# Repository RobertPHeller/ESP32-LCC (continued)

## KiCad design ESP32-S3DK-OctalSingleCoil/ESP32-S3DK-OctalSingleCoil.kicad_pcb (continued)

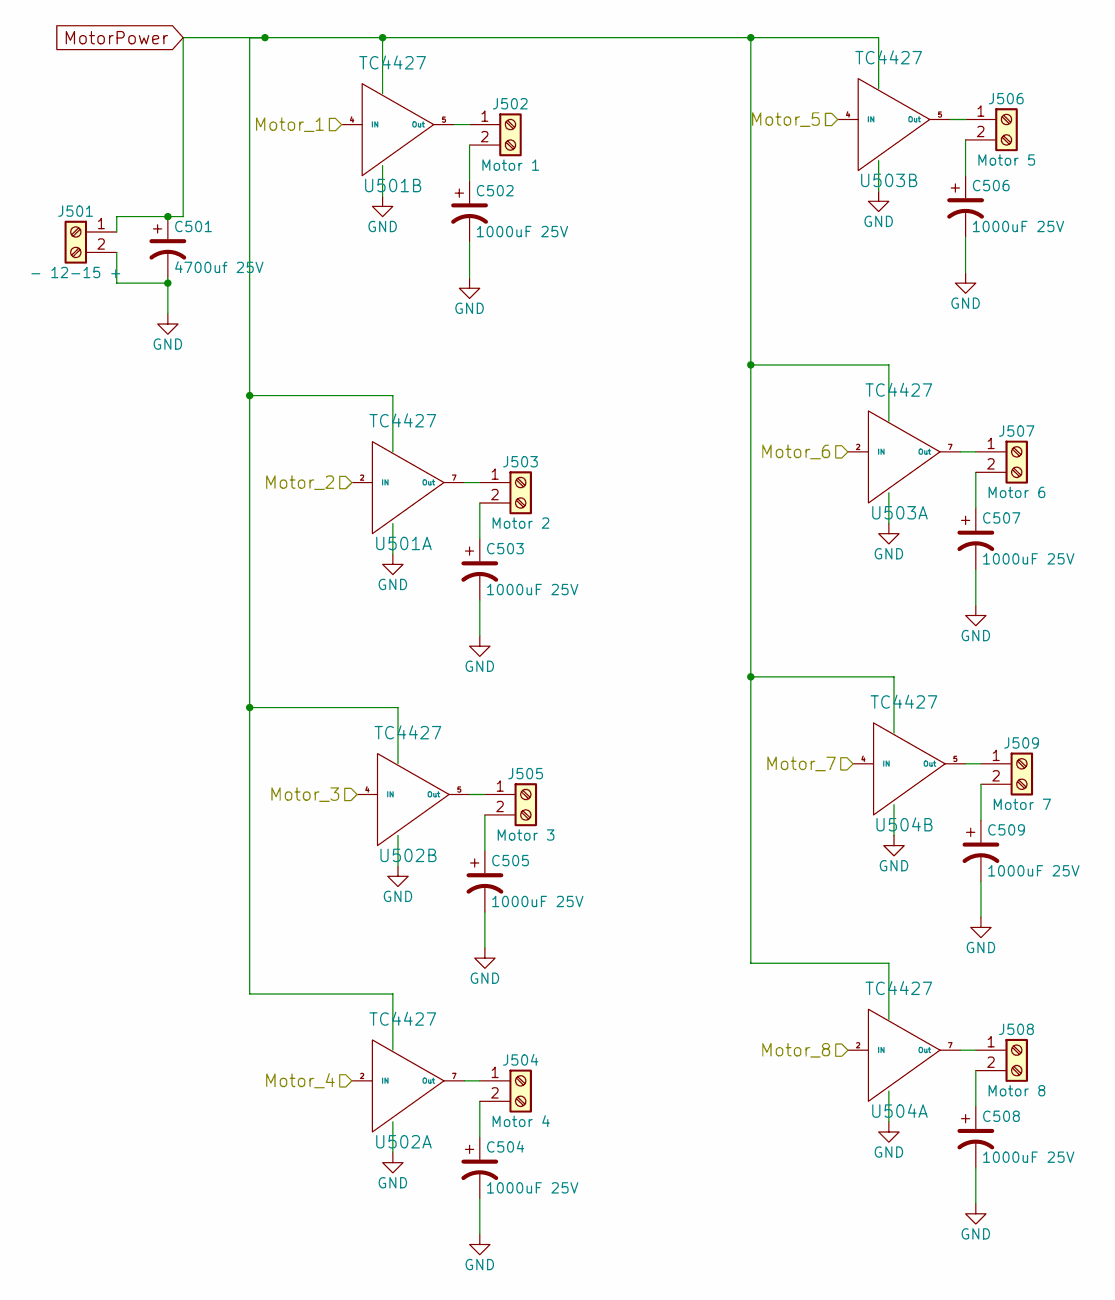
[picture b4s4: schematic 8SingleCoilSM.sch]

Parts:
C501: 4700uf 25V; EEEFK0J133SM; Mouser Part Number 667-EEE-FK1E472SM
C502, C503, C504, C505, C506, C507, C508, C509: 1000uF 25V; CP_Elec_10x10.5; Mouser Part Number 661-EMZS250ARA102MJA
J501: - 12-15 +; TerminalBlock_Pheonix_PT-3.5mm_2pol
J502: Motor 1; TerminalBlock_Pheonix_PT-3.5mm_2pol
J503: Motor 2; TerminalBlock_Pheonix_PT-3.5mm_2pol
J504: Motor 4; TerminalBlock_Pheonix_PT-3.5mm_2pol
J505: Motor 3; TerminalBlock_Pheonix_PT-3.5mm_2pol
J506: Motor 5; TerminalBlock_Pheonix_PT-3.5mm_2pol
J507: Motor 6; TerminalBlock_Pheonix_PT-3.5mm_2pol
J508: Motor 8; TerminalBlock_Pheonix_PT-3.5mm_2pol
J509: Motor 7; TerminalBlock_Pheonix_PT-3.5mm_2pol
U501, U502, U503, U504: TC4427; SOIC-8_3.9x4.9mm_Pitch1.27mm; Mouser Part Number 579-TC1427COA

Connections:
/MCU/GPIO3/Motor6: U503.2 (IN); also elsewhere on the board
/MCU/GPIO6/Motor1: U501.4 (IN); also elsewhere on the board
/MCU/GPIO7/Motor2: U501.2 (IN); also elsewhere on the board
/MCU/GPIO8/Motor5: U503.4 (IN); also elsewhere on the board
/MCU/GPIO9/Motor8: U504.2 (IN); also elsewhere on the board
/MCU/GPIO15/Motor3: U502.4 (IN); also elsewhere on the board
/MCU/GPIO16/Motor4: U502.2 (IN); also elsewhere on the board
/MCU/GPIO46/Motor7: U504.4 (IN); also elsewhere on the board
GND: C501.2, C502.2, C503.2, C504.2, C505.2, C506.2, C507.2, C508.2, C509.2, J501.2, U501.3 (GND), U502.3 (GND), U503.3 (GND), U504.3 (GND); also elsewhere on the board
MotorPower: C501.1, J501.1, U501.6 (Vdd), U502.6 (Vdd), U503.6 (Vdd), U504.6 (Vdd)
unnamed: C502.1, J502.2
unnamed: C503.1, J503.2
unnamed: C504.1, J504.2
unnamed: C505.1, J505.2
unnamed: C506.1, J506.2
unnamed: C507.1, J507.2
unnamed: C508.1, J508.2
unnamed: C509.1, J509.2
unnamed: J502.1, U501.5 (Out)
unnamed: J503.1, U501.7 (Out)
unnamed: J504.1, U502.7 (Out)
unnamed: J505.1, U502.5 (Out)
unnamed: J506.1, U503.5 (Out)
unnamed: J507.1, U503.7 (Out)
unnamed: J508.1, U504.7 (Out)
unnamed: J509.1, U504.5 (Out)

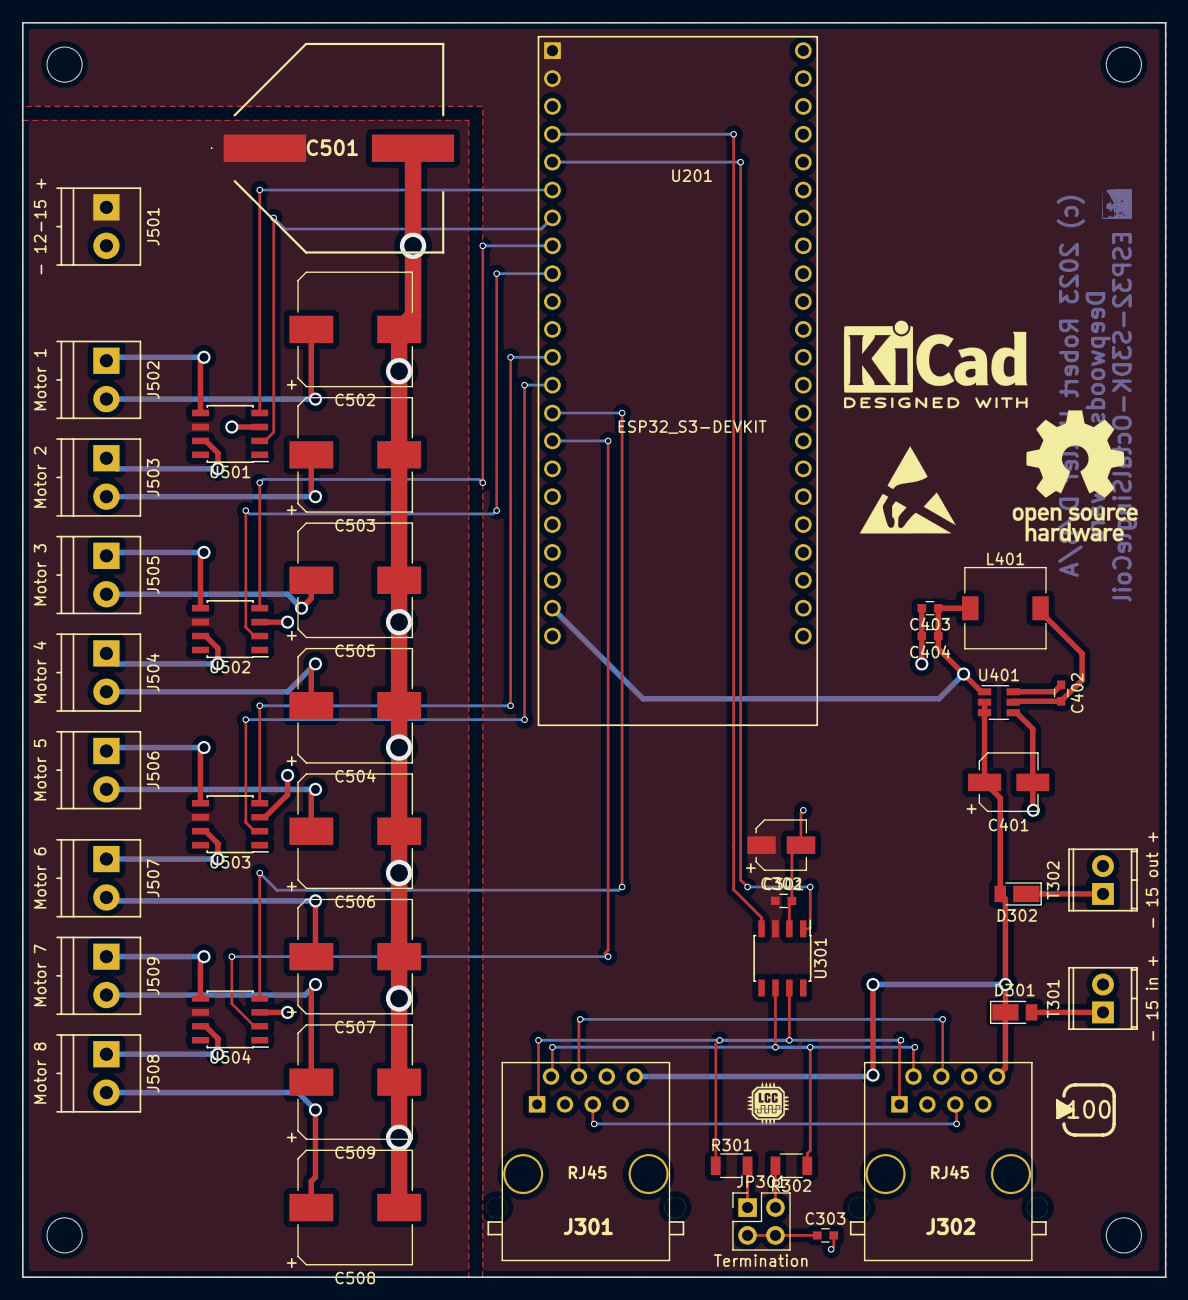
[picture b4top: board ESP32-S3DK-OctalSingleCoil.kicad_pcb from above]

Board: 2 copper layers, 104.1 x 114.3 mm, 42 parts (0 on the bottom side), 42 nets.

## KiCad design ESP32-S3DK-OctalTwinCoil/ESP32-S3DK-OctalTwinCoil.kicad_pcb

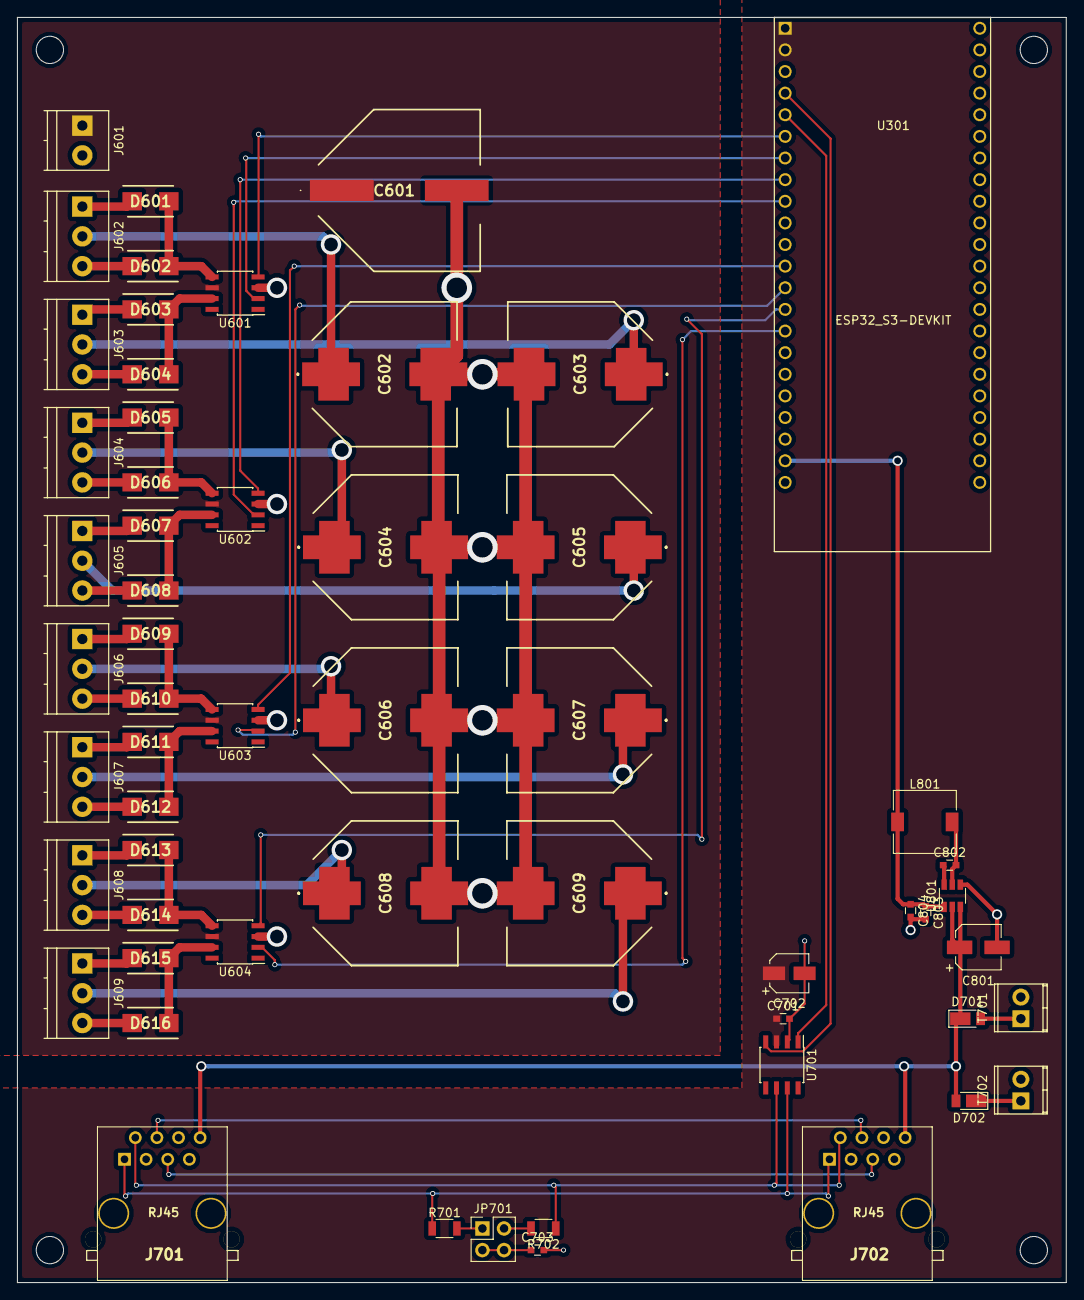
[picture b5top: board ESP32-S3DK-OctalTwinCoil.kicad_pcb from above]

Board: 2 copper layers, 123.2 x 148.6 mm, 58 parts (0 on the bottom side), 58 nets.

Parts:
C601: 4700uf 25V; EEEFK0J133SM
C602, C603, C604, C605, C606, C607, C608, C609: 2200uF 25V; EEEFK0J682AV
C701: .1 uf; C_0603
C702: 15 uf 15V; CP_Elec_4x5.7
C703: 47 nf; C_0603
C801: 10uf; CP_Elec_5x5.3
C802: 100nf; C_0603
C803, C804: 22uf; C_0603
D601, D602, D603, D604, D605, D606, D607, D608, D609, D610, D611, D612, D613, D614, D615, D616: S2A; DIOM5336X245N
D701, D702: DFLS240-7; D_PowerDI-123
J601: - 12-15 +; TerminalBlock_Pheonix_PT-3.5mm_2pol
J602: Motor 1; TerminalBlock_Pheonix_PT-3.5mm_3pol
J603: Motor 2; TerminalBlock_Pheonix_PT-3.5mm_3pol
J604: Motor 3; TerminalBlock_Pheonix_PT-3.5mm_3pol
J605: Motor 4; TerminalBlock_Pheonix_PT-3.5mm_3pol
J606: Motor 5; TerminalBlock_Pheonix_PT-3.5mm_3pol
J607: Motor 6; TerminalBlock_Pheonix_PT-3.5mm_3pol
J608: Motor 7; TerminalBlock_Pheonix_PT-3.5mm_3pol
J609: Motor 8; TerminalBlock_Pheonix_PT-3.5mm_3pol
J701, J702: RJ45; RJ45_8N-S
JP701: Termination; Pin_Header_Straight_2x02_Pitch2.54mm
L801: 4.7uH; L_7.3x7.3_H4.5
R701, R702: 60 Ohms; R_1206
T701: + 15 in -; TerminalBlock_Pheonix_MPT-2.54mm_2pol
T702: + 15 out -; TerminalBlock_Pheonix_MPT-2.54mm_2pol
U301: ESP32_S3-DEVKIT; ESP32-S3-Devkit-C
U601, U602, U603, U604: TC4427; SOIC-8_3.9x4.9mm_Pitch1.27mm
U701: TCAN332DR; SOIC-8_3.9x4.9mm_Pitch1.27mm
U801: AP63205; TSOT-23-6_MK06A

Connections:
+3V3: C701.1, C702.1, U301.1, U301.2, U701.3
+5V: C803.1, C804.1, L801.1, U301.21, U801.1
/CAN Transciver/CANH: J701.1, J702.1, R701.1, U701.7
/CAN Transciver/CANL: J701.2, J702.2, R702.1, U701.6
/CAN Transciver/CAN_RX: U301.4, U701.4
/CAN Transciver/CAN_TX: U301.5, U701.1
/MCU/GPIO3/Motor6: U301.13, U603.2
/MCU/GPIO6/Motor1: U301.6, U601.4
/MCU/GPIO7/Motor2: U301.7, U601.2
/MCU/GPIO8/Motor5: U301.12, U603.4
/MCU/GPIO9/Motor8: U301.15, U604.2
/MCU/GPIO15/Motor3: U301.8, U602.4
/MCU/GPIO16/Motor4: U301.9, U602.2
/MCU/GPIO46/Motor7: U301.14, U604.4
CAN +12V: C801.1, D701.1, D702.2, J701.8, J702.8, U801.2, U801.3
GND: C601.2, C602.2, C603.2, C604.2, C605.2, C606.2, C607.2, C608.2, C609.2, C701.2, C702.2, C703.2, C801.2, C803.2, C804.2, J601.2, J701.3, J701.6, J701.7, J702.3, J702.6, J702.7, T701.2, T702.2, U301.22, U301.23, U301.24, U301.44, U601.3, U602.3, U603.3, U604.3, U701.2, U801.4
MotorPower: C601.1, J601.1, U601.6, U602.6, U603.6, U604.6
unnamed: C602.1, J602.2
unnamed: C603.1, J603.2
unnamed: C604.1, J604.2
unnamed: C605.1, J605.2
unnamed: C606.1, J606.2
unnamed: C607.1, J607.2
unnamed: C608.1, J608.2
unnamed: C609.1, J609.2
unnamed: C703.1, JP701.3, JP701.4
unnamed: C802.1, U801.6
unnamed: C802.2, L801.2, U801.5
unnamed: D601.1, J602.1
unnamed: D601.2, D602.1, U601.5
unnamed: D602.2, J602.3
unnamed: D603.1, J603.1
unnamed: D603.2, D604.1, U601.7
unnamed: D604.2, J603.3
unnamed: D605.1, J604.1
unnamed: D605.2, D606.1, U602.5
unnamed: D606.2, J604.3
unnamed: D607.1, J605.1
unnamed: D607.2, D608.1, U602.7
unnamed: D608.2, J605.3
unnamed: D609.1, J606.1
unnamed: D609.2, D610.1, U603.5
unnamed: D610.2, J606.3
unnamed: D611.1, J607.1
unnamed: D611.2, D612.1, U603.7
unnamed: D612.2, J607.3
unnamed: D613.1, J608.1
unnamed: D613.2, D614.1, U604.5
unnamed: D614.2, J608.3
unnamed: D615.1, J609.1
unnamed: D615.2, D616.1, U604.7
unnamed: D616.2, J609.3
unnamed: D701.2, T701.1
unnamed: D702.1, T702.1
unnamed: J701.4, J702.4
unnamed: J701.5, J702.5
unnamed: JP701.1, R701.2
unnamed: JP701.2, R702.2

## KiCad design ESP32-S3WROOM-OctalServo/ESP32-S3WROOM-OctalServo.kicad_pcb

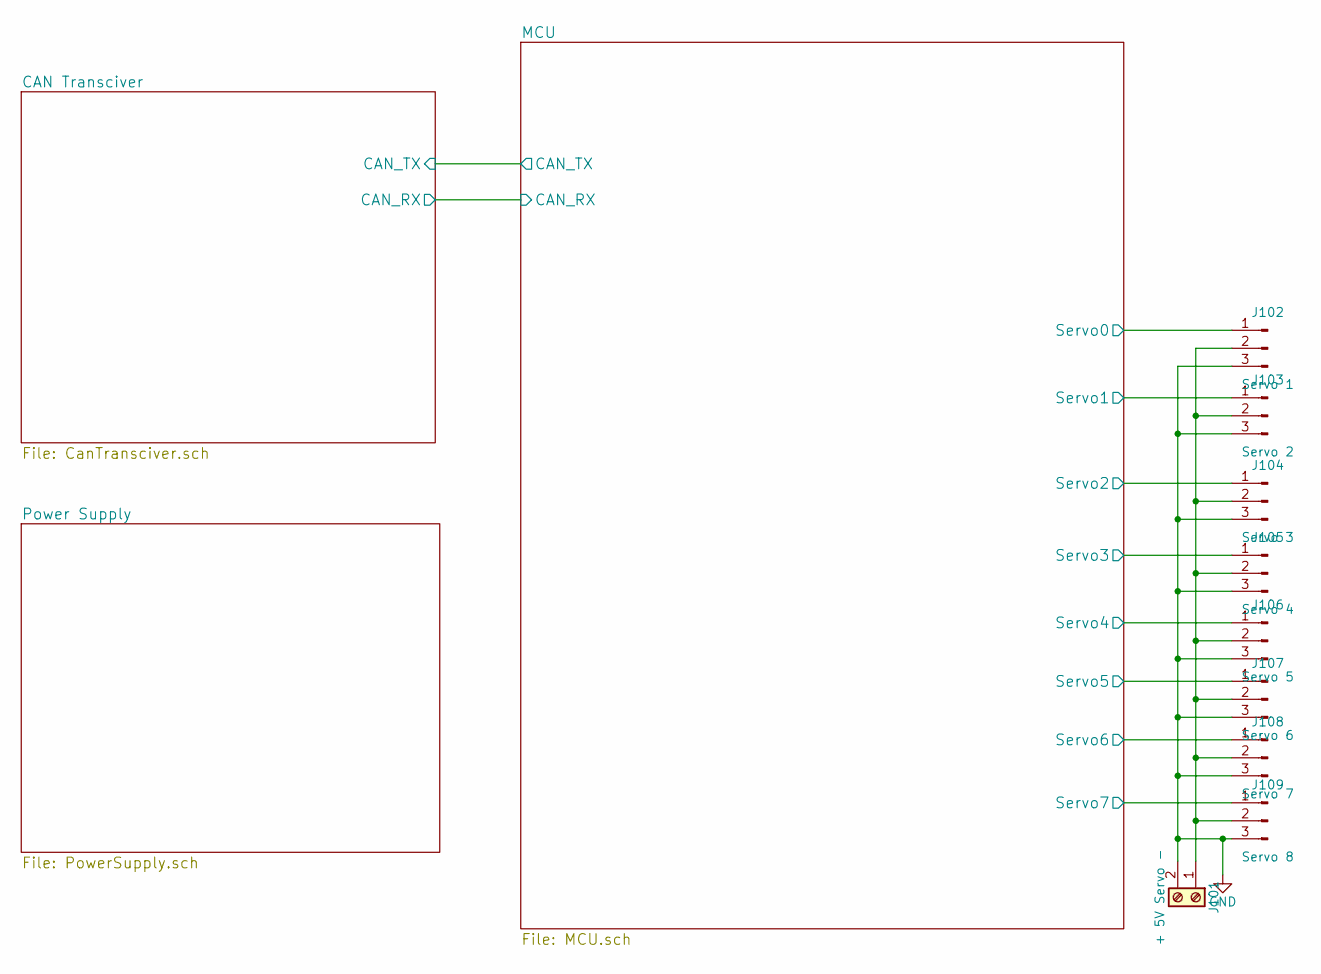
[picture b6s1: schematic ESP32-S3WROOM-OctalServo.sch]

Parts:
J101: + 5V Servo -; TerminalBlock_Pheonix_PT-3.5mm_2pol
J102: Servo 1; Pin_Header_Straight_1x03_Pitch2.54mm
J103: Servo 2; Pin_Header_Straight_1x03_Pitch2.54mm
J104: Servo 3; Pin_Header_Straight_1x03_Pitch2.54mm
J105: Servo 4; Pin_Header_Straight_1x03_Pitch2.54mm
J106: Servo 5; Pin_Header_Straight_1x03_Pitch2.54mm
J107: Servo 6; Pin_Header_Straight_1x03_Pitch2.54mm
J108: Servo 7; Pin_Header_Straight_1x03_Pitch2.54mm
J109: Servo 8; Pin_Header_Straight_1x03_Pitch2.54mm

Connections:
/MCU/Servo0: J102.1; also elsewhere on the board
/MCU/Servo1: J103.1; also elsewhere on the board
/MCU/Servo2: J104.1; also elsewhere on the board
/MCU/Servo3: J105.1; also elsewhere on the board
/MCU/Servo4: J106.1; also elsewhere on the board
/MCU/Servo5: J107.1; also elsewhere on the board
/MCU/Servo6: J108.1; also elsewhere on the board
/MCU/Servo7: J109.1; also elsewhere on the board
GND: J101.2, J102.3, J103.3, J104.3, J105.3, J106.3, J107.3, J108.3, J109.3; also elsewhere on the board
unnamed: J101.1, J102.2, J103.2, J104.2, J105.2, J106.2, J107.2, J108.2, J109.2

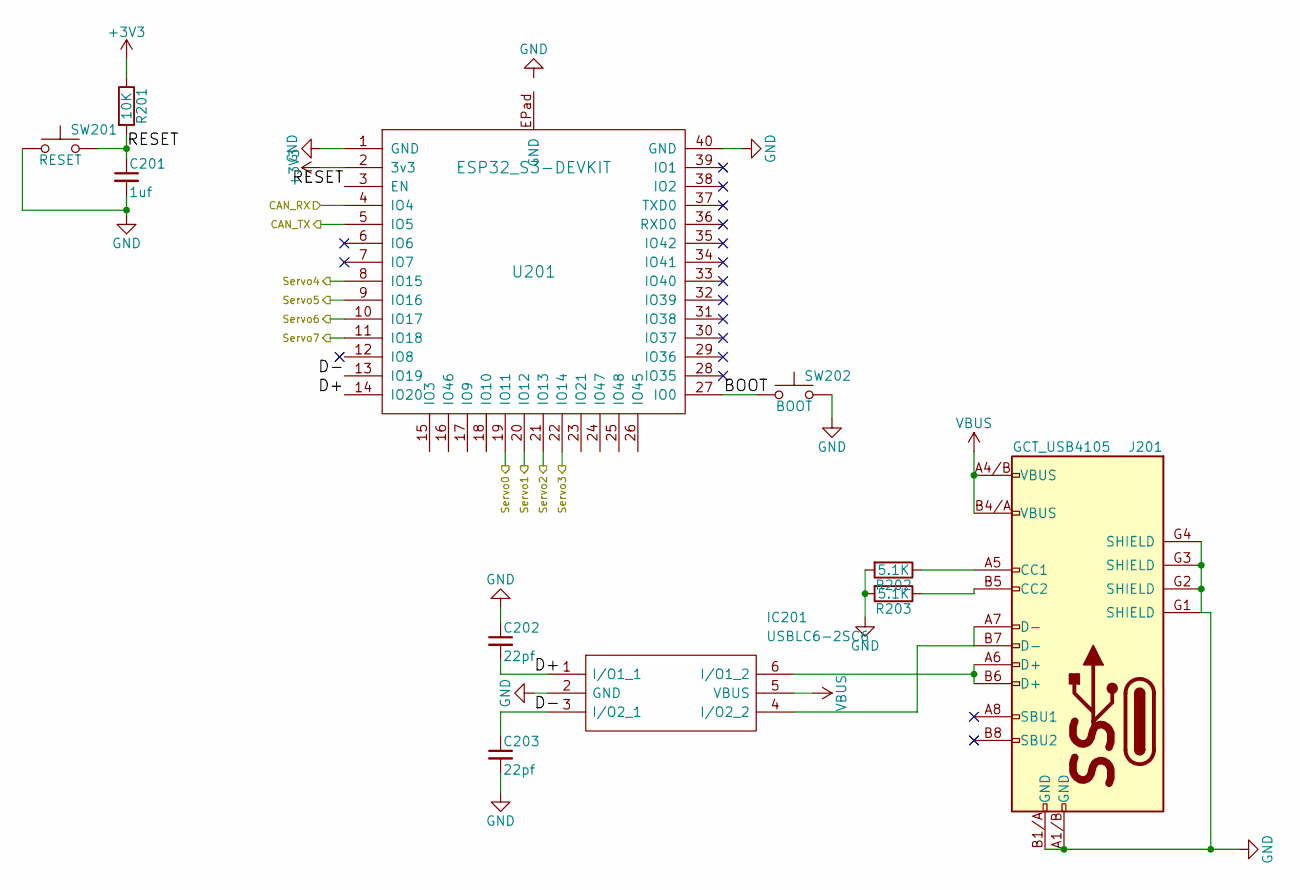
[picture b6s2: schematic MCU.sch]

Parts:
C201: 1uf; C_0603_HandSoldering; Mouser Part Number 187-CL10B104KA8NFNC
C202, C203: 22pf; C_0603_HandSoldering; Mouser Part Number 710-885012006019
IC201: USBLC6-2SC6; SOT-23-6; Mouser2 Part Number 511-USBLC6-2SC6
J201: GCT_USB4105; GCT_USB4105-GF-A; Mouser Part Number 640-USB4105-GF-A-120
R201: 10K; R_0603_HandSoldering; Mouser Part Number 71-CRCW060310K0JNEBC
R202, R203: 5.1K; R_0603_HandSoldering; Mouser Part Number 603-AC0603FR-075K1L
SW201: RESET; SW_SPST_FSMSM; Mouser Part Number 506-FSMSM
SW202: BOOT; SW_SPST_FSMSM; Mouser Part Number 506-FSMSM
U201: ESP32_S3-DEVKIT; ESP32_S3_WROOM-1

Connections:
+3V3: R201.1, U201.2 (3v3); also elsewhere on the board
/CAN Transciver/CAN_RX: U201.4 (IO4); also elsewhere on the board
/CAN Transciver/CAN_TX: U201.5 (IO5); also elsewhere on the board
/MCU/BOOT: SW202.1, U201.27 (IO0)
/MCU/D+: C202.2, IC201.1 (I/O1_1), U201.14 (IO20)
/MCU/D-: C203.1, IC201.3 (I/O2_1), U201.13 (IO19)
/MCU/RESET: C201.1, R201.2, SW201.2, U201.3 (EN)
/MCU/Servo0: U201.19 (IO11); also elsewhere on the board
/MCU/Servo1: U201.20 (IO12); also elsewhere on the board
/MCU/Servo2: U201.21 (IO13); also elsewhere on the board
/MCU/Servo3: U201.22 (IO14); also elsewhere on the board
/MCU/Servo4: U201.8 (IO15); also elsewhere on the board
/MCU/Servo5: U201.9 (IO16); also elsewhere on the board
/MCU/Servo6: U201.10 (IO17); also elsewhere on the board
/MCU/Servo7: U201.11 (IO18); also elsewhere on the board
GND: C201.2, C202.1, C203.2, IC201.2 (GND), J201.A1/B (GND), J201.B1/A (GND), J201.G1 (SHIELD), J201.G2 (SHIELD), J201.G3 (SHIELD), J201.G4 (SHIELD), R202.2, R203.2, SW201.1, SW202.2, U201.1 (GND), U201.40 (GND); also elsewhere on the board
unnamed: IC201.4 (I/O2_2), J201.A7 (D-), J201.B7 (D-)
unnamed: IC201.6 (I/O1_2), J201.A6 (D+), J201.B6 (D+)
unnamed: J201.A5 (CC1), R202.1
unnamed: J201.B5 (CC2), R203.1
VBUS: IC201.5 (VBUS), J201.A4/B (VBUS), J201.B4/A (VBUS); also elsewhere on the board

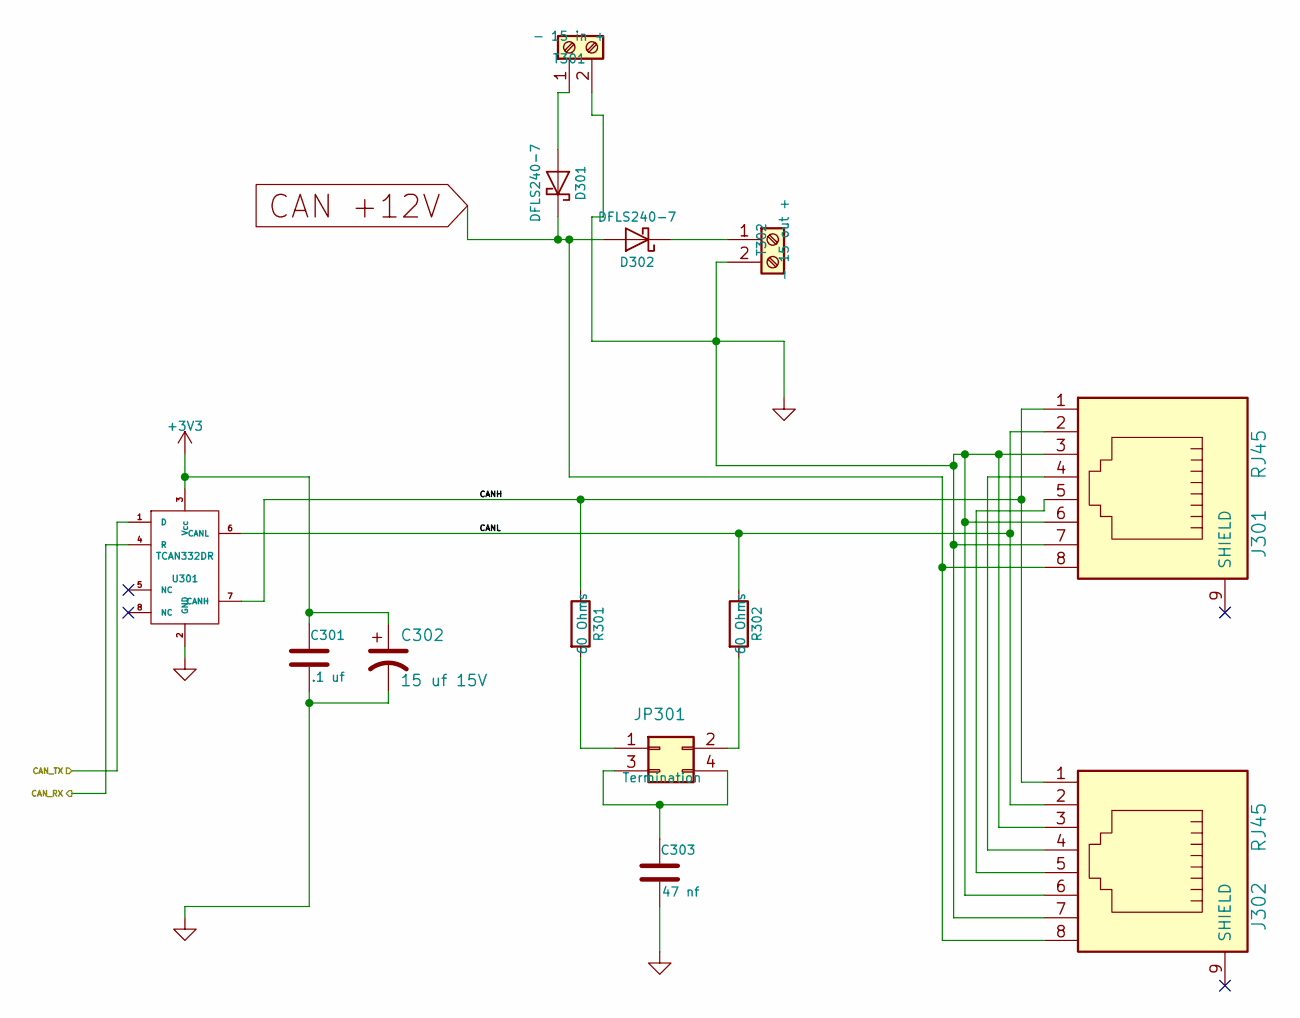
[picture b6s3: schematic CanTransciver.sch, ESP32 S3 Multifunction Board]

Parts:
C301: .1 uf; C_0603; Mouser Part Number 710-885012206095
C302: 15 uf 15V; CP_Elec_4x5.7; Mouser Part Number 647-UUD1C150MCL
C303: 47 nf; C_0603; Mouser Part Number 710-885012206093
D301, D302: DFLS240-7; D_PowerDI-123; Mouser Part Number 621-DFLS240-7
J301, J302: RJ45; RJ45_8N-S; Mouser Part Number 710-615008144221
JP301: Termination; Pin_Header_Straight_2x02_Pitch2.54mm; Mouser Part Number 649-67997-404HLF
R301, R302: 60 Ohms; R_1206; Mouser Part Number 71-CRCW120660R0KNAIF
T301: - 15 in +; TerminalBlock_Pheonix_MPT-2.54mm_2pol; Mouser Part Number 651-1725656
T302: - 15 out +; TerminalBlock_Pheonix_MPT-2.54mm_2pol; Mouser Part Number 651-1725656
U301: TCAN332DR; SOIC-8_3.9x4.9mm_Pitch1.27mm; Mouser Part Number 595-TCAN332DR

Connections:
+3V3: C301.1, C302.1, U301.3 (Vcc); also elsewhere on the board
/CAN Transciver/CANH: J301.1, J302.1, R301.1, U301.7 (CANH)
/CAN Transciver/CANL: J301.2, J302.2, R302.1, U301.6 (CANL)
/CAN Transciver/CAN_RX: U301.4 (R); also elsewhere on the board
/CAN Transciver/CAN_TX: U301.1 (D); also elsewhere on the board
CAN +12V: D301.1 (K), D302.2 (A), J301.8, J302.8; also elsewhere on the board
GND: C301.2, C302.2, C303.2, J301.3, J301.6, J301.7, J302.3, J302.6, J302.7, T301.2, T302.2, U301.2 (GND); also elsewhere on the board
unnamed: C303.1, JP301.3, JP301.4
unnamed: D301.2 (A), T301.1
unnamed: D302.1 (K), T302.1
unnamed: J301.4, J302.4
unnamed: J301.5, J302.5
unnamed: JP301.1, R301.2
unnamed: JP301.2, R302.2

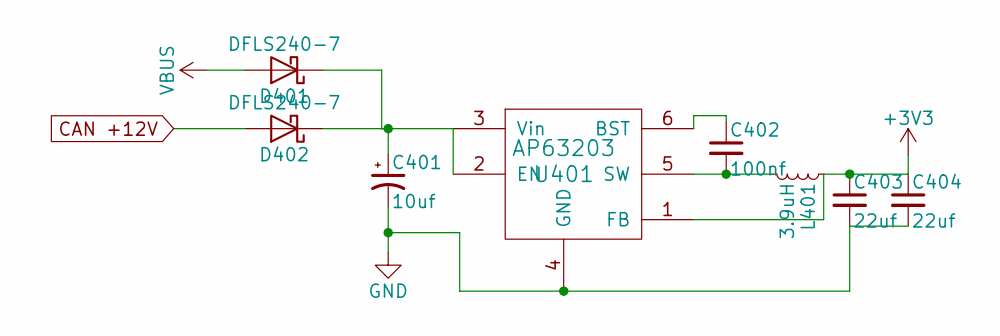
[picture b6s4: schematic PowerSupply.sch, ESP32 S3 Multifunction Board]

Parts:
C401: 10uf; CP_Elec_5x5.3; Mouser Part Number 710-865230542002
C402: 100nf; C_0603; Mouser Part Number 710-885012206020
C403, C404: 22uf; C_0603; Mouser Part Number 603-CC0603MRX6S5B226
D401, D402: DFLS240-7; D_PowerDI-123; Mouser Part Number 621-DFLS240-7
L401: 3.9uH; L_7.3x7.3_H4.5; Mouser Part Number 81-B1047AS-3R6NP3
U401: AP63203; TSOT-23-6_MK06A; Mouser Part Number 621-AP63203QWU-7

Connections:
+3V3: C403.1, C404.1, L401.1, U401.1 (FB); also elsewhere on the board
CAN +12V: D402.2 (A); also elsewhere on the board
GND: C401.2, C403.2, C404.2, U401.4 (GND); also elsewhere on the board
unnamed: C401.1, D401.1 (K), D402.1 (K), U401.2 (EN), U401.3 (Vin)
unnamed: C402.1, U401.6 (BST)
unnamed: C402.2, L401.2, U401.5 (SW)
VBUS: D401.2 (A); also elsewhere on the board

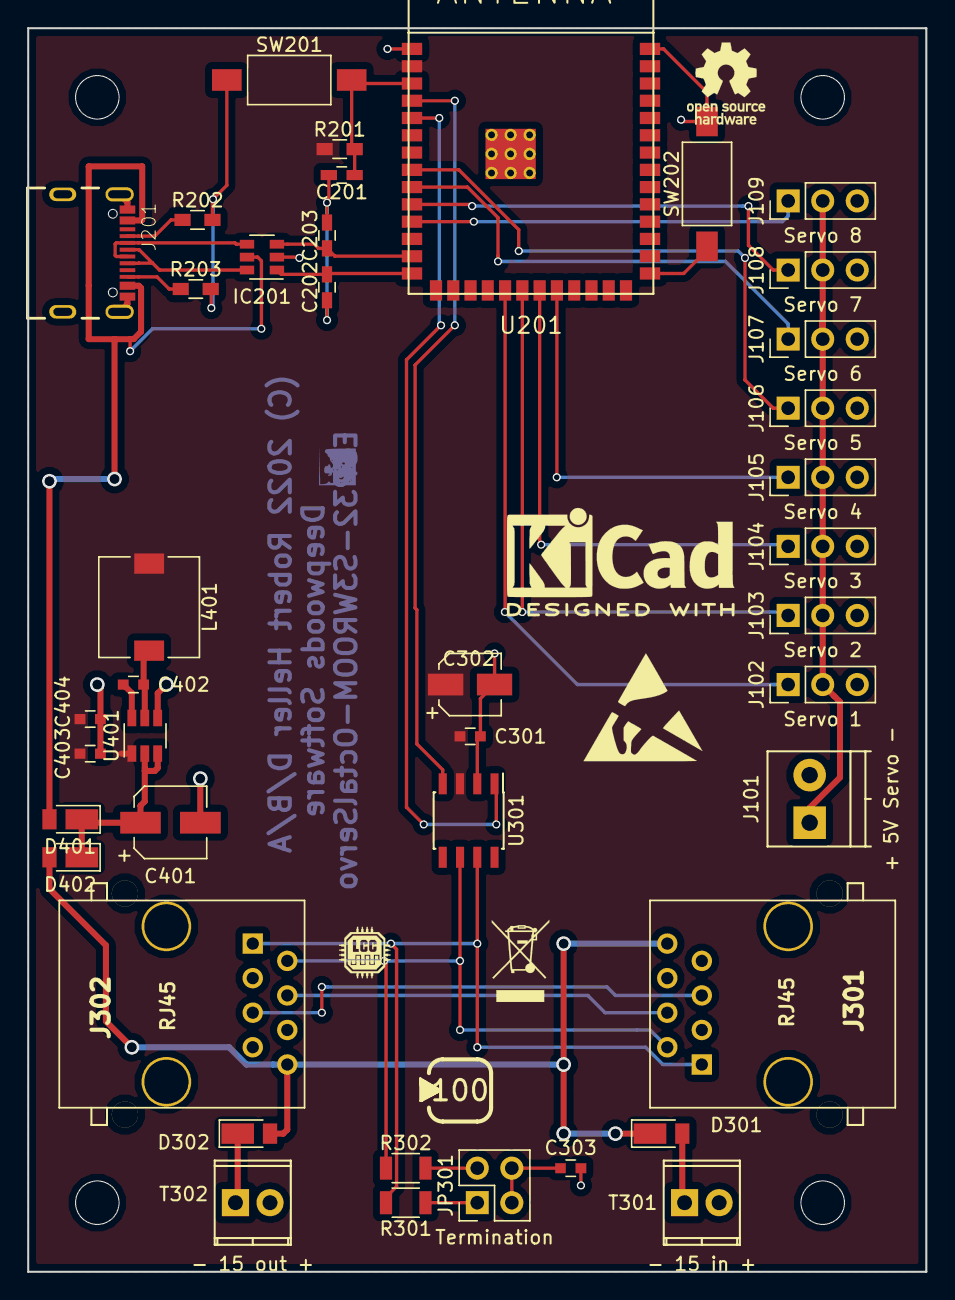
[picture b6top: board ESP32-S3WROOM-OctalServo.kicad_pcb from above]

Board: 2 copper layers, 66.0 x 91.4 mm, 41 parts (0 on the bottom side), 35 nets.
